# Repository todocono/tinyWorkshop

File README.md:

# tinyWorkshop
Designed by Rodolfo Cossovich @NYUShanghai

## Programming - 2019/10/15

LED Blink  
What’s under the hood: https://www.arduino.cc/en/uploads/Main/arduino-uno-schematic.pdf  
What “they don’t tell you”: https://cdn.sparkfun.com/assets/c/a/8/e/4/Atmel-42735-8-bit-AVR-Microcontroller-ATmega328-328P_Datasheet.pdf  
Diversity: https://ww1.microchip.com/downloads/en/DeviceDoc/Atmel-2586-AVR-8-bit-Microcontroller-ATtiny25-ATtiny45-ATtiny85_Datasheet.pdf  
How Arduinos are born: https://en.wikipedia.org/wiki/In-system_programming  
Hackers welcome: https://www.arduino.cc/en/tutorial/arduinoISP  
These pins: https://www.instructables.com/id/Program-an-ATtiny-with-Arduino/  
Bypass!!! Capacitor 10uF  
This board: https://raw.githubusercontent.com/damellis/attiny/ide-1.6.x-boards-manager/package_damellis_attiny_index.json  
LED Blink  
8MHz boot loader: LED Blink  
analogWrite  
Stingy Watchdog: https://www.insidegadgets.com/2011/02/05/reduce-attiny-power-consumption-by-sleeping-with-the-watchdog-timer/  

## PCB Design - 2019/10/22

CAD Software: https://predictabledesigns.com/pcb-design-software-which-one-is-best/  
Eagle: https://www.autodesk.com/products/eagle/free-download  
Help from Sparkfun: https://learn.sparkfun.com/tutorials/how-to-install-and-setup-eagle  
Help for the help: https://learn.sparkfun.com/tutorials/pcb-basics/all  
ATtiny85 footprint: https://www.snapeda.com/parts/ATTINY85-20PU/Microchip/view-part/  
LEDs & everything else: https://github.com/adafruit/Adafruit-Eagle-Library  
Measure well or measure twice: PRINT!  

## Manufacturing - 2019/10/29

Ironing your PCB: https://www.sparkfun.com/news/2116?_ga=2.74353041.282288770.1571127757-1077704488.1567749628  
ProtoMat 43: https://www.lpkfusa.com/products/pcb_prototyping/machines/protomat_s64/  
Exporting circuits -old style-: http://optics.eee.nottingham.ac.uk/eagle/eagle2lpkf_at_eee.html  
Western approach: https://oshpark.com/  
PCB paradise: https://www.jdbpcb.com/

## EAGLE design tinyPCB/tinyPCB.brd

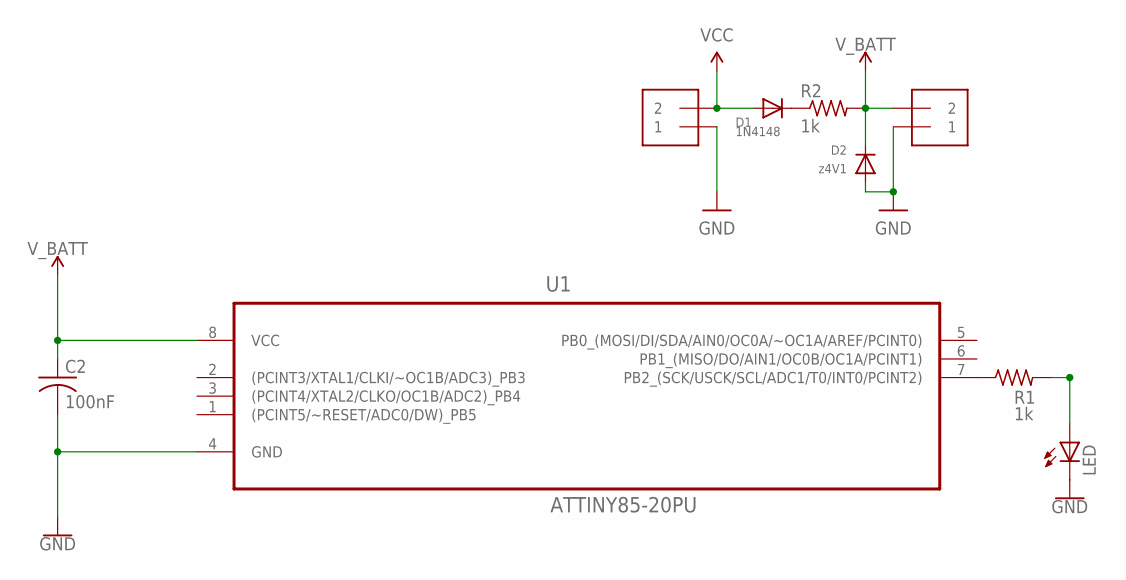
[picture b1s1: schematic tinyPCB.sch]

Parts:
BAT: 1X2-3.5MM
C2: 100nF; C050-025X075
CHG: 1X2-3.5MM
D1: 1N4148; DO-1N4148
D2: z4V1; DO-1N4148
LED: LED5MM
R1, R2: 1k; 0204/7
U1: ATTINY85-20PU; DIP254P762X533-8

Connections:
GND: BAT.1, C2.2, CHG.1, D2.A, LED.K (C), U1.4 (GND)
unnamed: R1.1, U1.7 (PB2_(SCK/USCK/SCL/ADC1/T0/INT0/PCINT2))
unnamed: LED.A, R1.2
unnamed: D1.C, R2.1
VCC: CHG.2, D1.A
V_BATT: BAT.2, C2.1, D2.C, R2.2, U1.8 (VCC)

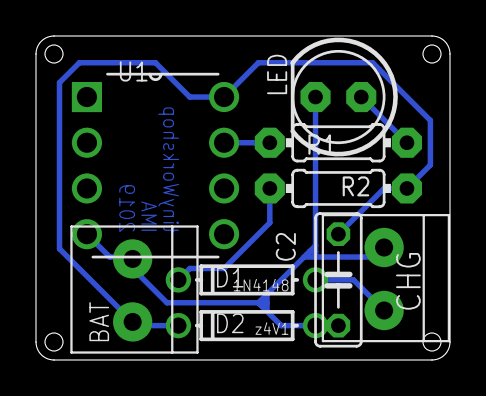
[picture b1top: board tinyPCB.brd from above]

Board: 2 copper layers, 23.0 x 18.0 mm, 9 parts (0 on the bottom side), 6 nets.

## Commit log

2019-10-15 minor change

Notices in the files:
parts and their libraries:
SparkFun-PowerSymbols: Licensing: Creative Commons ShareAlike 4.0 International - https://creativecommons.org/licenses/by-sa/4.0
